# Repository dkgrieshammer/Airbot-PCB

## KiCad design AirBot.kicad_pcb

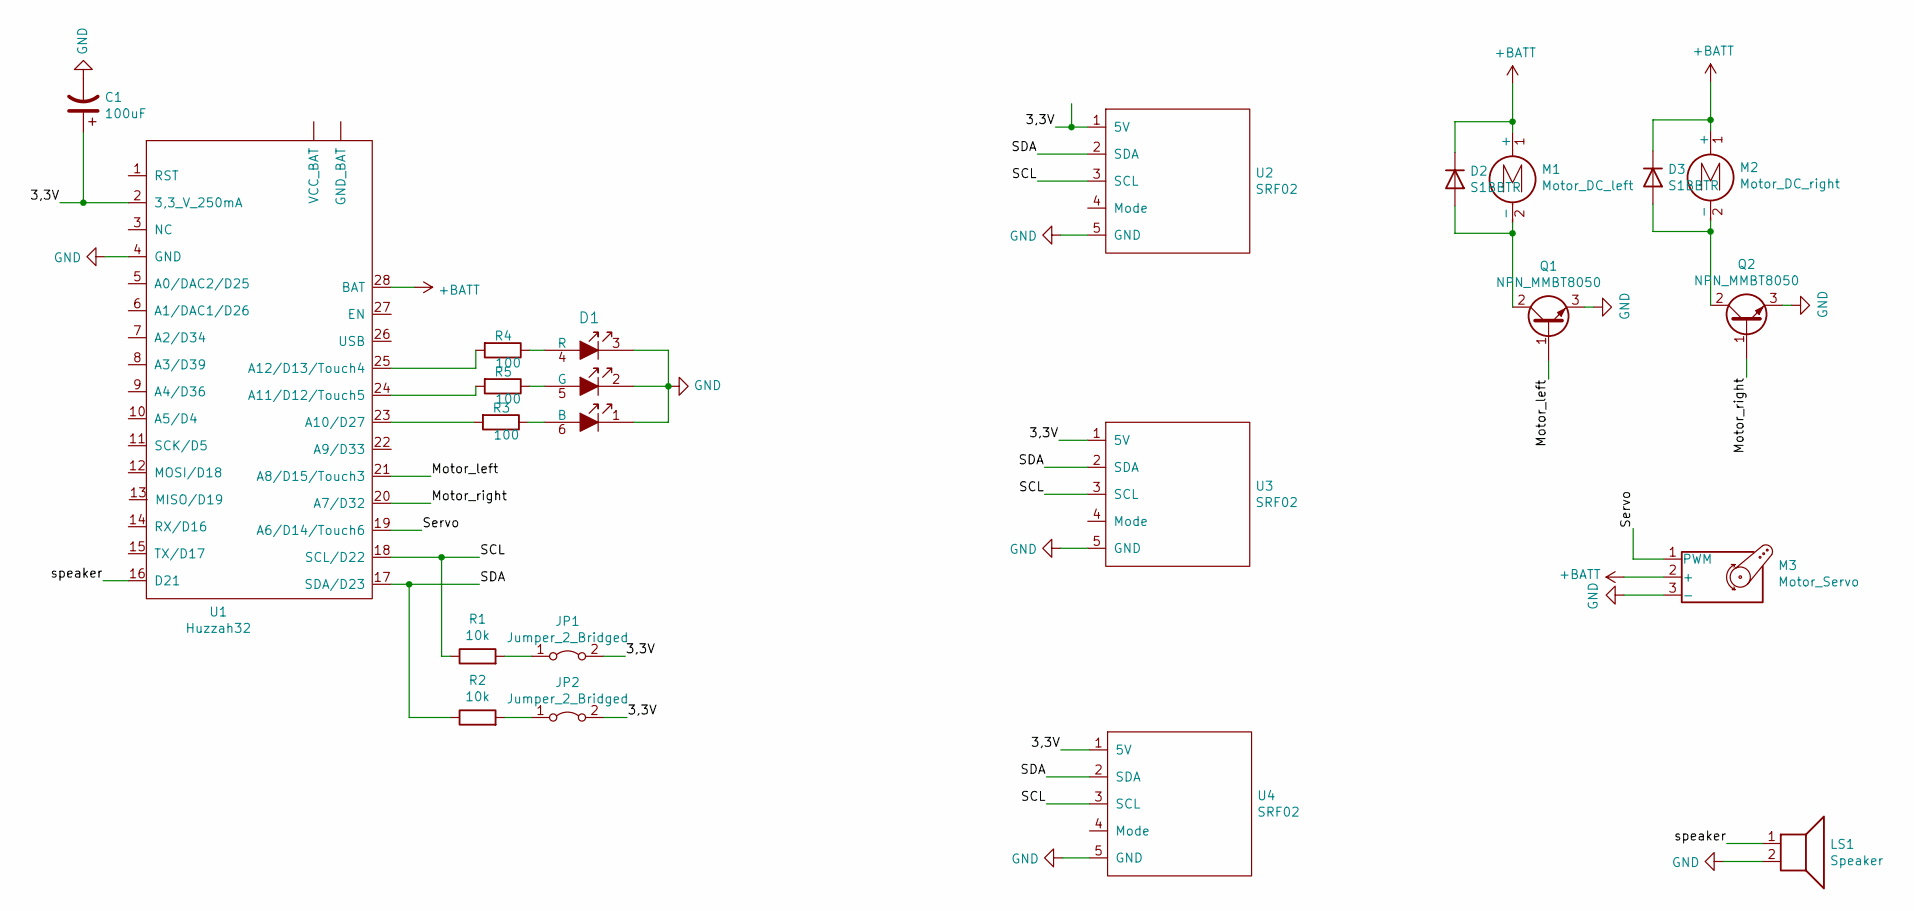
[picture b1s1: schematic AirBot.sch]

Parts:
C1: 100uF; C_1206_3216Metric
D1: ASMB-TTB0-0A3A2; 6-PLCC_3.5x3.5mm; MPN ASMB-TTB0-0A3A2; Digi-Key_PN 516-3281-1-ND
D2, D3: S1BBTR; D_SMB
JP1, JP2: Jumper_2_Bridged; SolderJumper-2_P1.3mm_Bridged_Pad1.0x1.5mm
LS1: Speaker; PinHeader_1x02_P2.54mm_Vertical
M1: Motor_DC_left; PinHeader_1x02_P2.54mm_Vertical
M2: Motor_DC_right; PinHeader_1x02_P2.54mm_Vertical
M3: Motor_Servo; PinHeader_1x03_P2.54mm_Vertical
Q1, Q2: NPN_MMBT8050; SOT-23
R1, R2: 10k; R_0603_1608Metric
R3, R4, R5: 100; R_0603_1608Metric
U1: Huzzah32
U2, U3, U4: SRF02; PinHeader_1x05_P2.54mm_Vertical

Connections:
+BATT: D2.1 (K), D3.1 (K), M1.1 (+), M2.1 (+), M3.2 (+), U1.28 (BAT)
/3,3V: C1.1, JP1.2 (B), JP2.2 (B), U1.2 (3,3_V_250mA), U2.1 (5V), U3.1 (5V), U4.1 (5V)
/Motor_left: Q1.1 (B), U1.21 (A8/D15/Touch3)
/Motor_right: Q2.1 (B), U1.20 (A7/D32)
/SCL: R1.1, U1.18 (SCL/D22), U2.3 (SCL), U3.3 (SCL), U4.3 (SCL)
/SDA: R2.1, U1.17 (SDA/D23), U2.2 (SDA), U3.2 (SDA), U4.2 (SDA)
/Servo: M3.1 (PWM), U1.19 (A6/D14/Touch6)
/speaker: LS1.1, U1.16 (D21)
GND: C1.2, D1.1, D1.2, D1.3, LS1.2, M3.3 (-), Q1.3 (E), Q2.3 (E), U1.4 (GND), U2.5 (GND), U3.5 (GND), U4.5 (GND)
unnamed: D1.4 (R), R4.1
unnamed: D1.5 (G), R5.1
unnamed: D1.6 (B), R3.1
unnamed: D2.2 (A), M1.2 (-), Q1.2 (C)
unnamed: D3.2 (A), M2.2 (-), Q2.2 (C)
unnamed: JP1.1 (A), R1.2
unnamed: JP2.1 (A), R2.2
unnamed: R3.2, U1.23 (A10/D27)
unnamed: R4.2, U1.25 (A12/D13/Touch4)
unnamed: R5.2, U1.24 (A11/D12/Touch5)

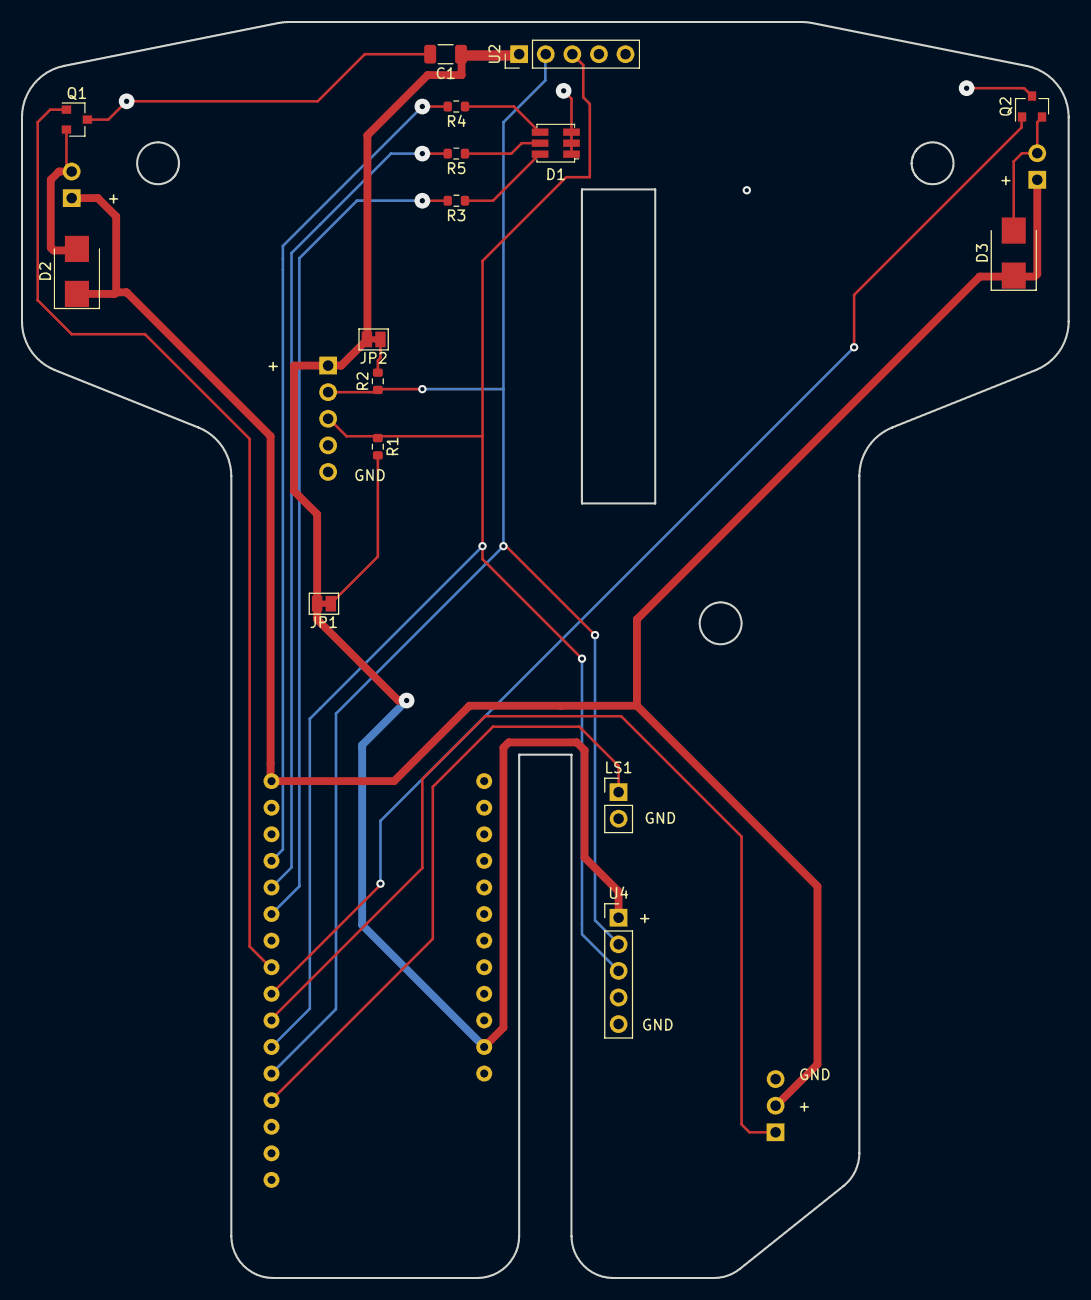
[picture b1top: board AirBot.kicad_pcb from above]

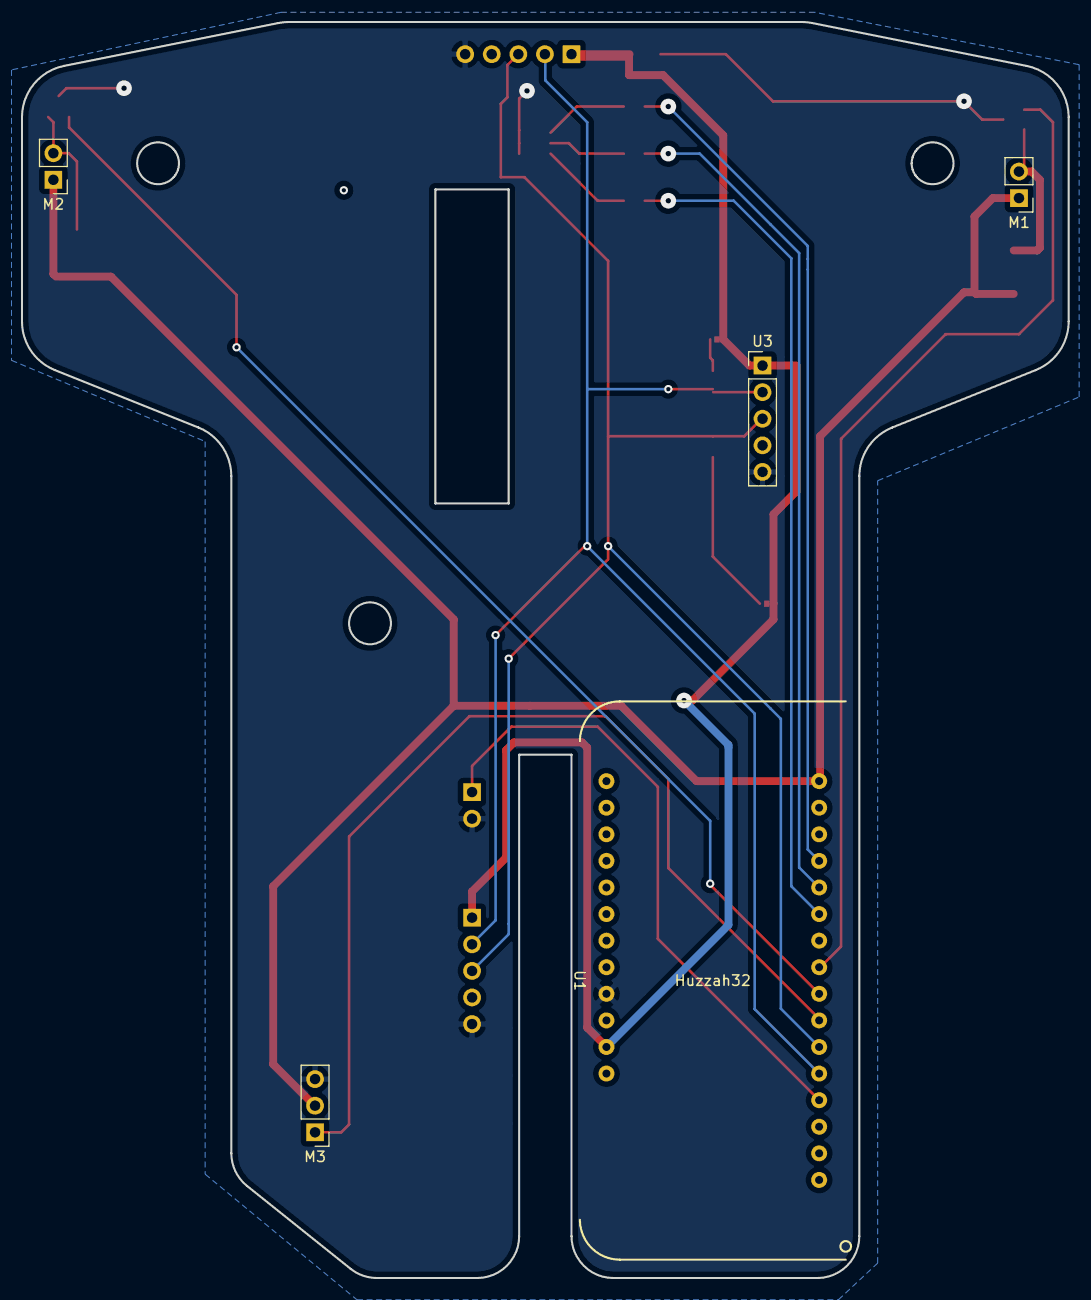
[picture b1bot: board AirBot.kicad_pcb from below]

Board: 2 copper layers, 100.0 x 120.0 mm, 21 parts (5 on the bottom side), 19 nets.

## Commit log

2021-06-02 Airbot V1
2021-06-19 Corrected Footprint Numbers according to Blueprint

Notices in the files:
AirBot.kicad_pcb:
License: CC BY 4.0
AirBot.sch:
creativecommons.org/licenses/by/4.0
